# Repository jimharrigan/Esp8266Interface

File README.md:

# Esp8266Interface

A WiFi bridge between a dry-contact (or opto-isolated) signal and MQTT / HTTP, built
around an ESP-01 module. It reports the state of an external input to an MQTT topic
and/or a pair of webhook URLs, and drives a relay output in response to MQTT messages
or a polled URL.

Typical use is retrofitting network connectivity onto existing wired equipment —
a doorbell transformer, an alarm panel output, a gate contact — without modifying it.

The repository contains both halves of the project:

| Path | Contents |
| --- | --- |
| `Esp8266Interface.ino` | The Arduino firmware (single sketch) |
| `Esp8266Interface/` | KiCad schematic and PCB for the carrier board |
| `Esp8266Interface/production/` | Fabrication output: gerbers, BOM, positions, IPC netlist |
| `Esp8266Interface.sln`, `*.vcxproj` | Visual Studio + [Visual Micro](https://www.visualmicro.com/) project |
| `Esp8266Interface/test/` | Scratch KiCad project, not part of the build |

## How it works

**Input → network.** An external signal pulls `GPIO3` low, either through the on-board
PC817 optocoupler (from the `HV In` header) or by a plain contact closure on the `In3`
header. A pin-change interrupt records the new level; the main loop notices the change
and:

- publishes `Trigger` (pin low) or `Reset` (pin high) to the configured MQTT topic, and
- issues an HTTP `GET` to the configured trigger URL or reset URL.

**Network → output.** The firmware subscribes to a control topic. A payload of `1` or
`trigger` drives `GPIO1` high; anything else drives it low. `GPIO1` gates a 2N7000
low-side switch on the `Rly` header, so this is intended to energise a relay coil. The
new state is echoed back to the status topic as `Output 1` / `Output 0`.

The same output can instead — or as well — be driven by polling. If a control URL is
configured, the board fetches it every 2 s and looks at the reply: a body containing
`Trigger` closes the relay, one containing `Reset` opens it. This suits a far end that
has no MQTT broker and cannot reach in to the board, only be asked.

## Hardware

### Connectors

Silkscreen labels come from the BOM; the descriptions below are derived from the netlist.

| Ref | Label | Function |
| --- | --- | --- |
| J1 | `ESP01` | 2x4 socket for the ESP-01 module |
| J4 | `Pin` | **Power in.** Pin 1 GND, pin 2 raw DC into the LM1084-3.3 regulator |
| J5 | `Pout` | **Power out.** Pin 1 raw input rail, pin 2 regulated +3.3 V |
| J7 | `HV In` | **Isolated sense input.** Pin 1 is the common return; pin 2 feeds the optocoupler through R2 (1 k), pin 3 through R3 (68 k) + R2 for a higher-voltage source. D2 (1N4004) rectifies, so an AC source works; D1 (zener) and C5 clamp and smooth what reaches the PC817 LED via R1 (2.2 k) |
| J2 | `In3` | **Non-isolated input.** Shorting the two pins pulls `GPIO3` to GND, in parallel with the optocoupler |
| J3 | `In` | **Config-portal button.** Shorts `GPIO0` to `GPIO2`, which the firmware holds low after boot |
| J6 | `Rly` | **Relay output.** Pin 1 is the raw input rail, pin 2 the 2N7000 drain; D3 (1N4001) is the flyback diode across the coil |
| SW1 | — | Momentary **reset** for the ESP-01 (`RST` to GND) |

The zener D1 has no value in the BOM, so the usable voltage range of each `HV In` tap
depends on the part actually fitted. Work out the range for your source before relying
on it, and treat anything on `HV In` as hazardous unless you know otherwise — nothing on
the board isolates `HV In` from its own source, only from the ESP side.

### ESP-01 pin usage

| Pin | Direction | Use |
| --- | --- | --- |
| `GPIO0` | input, 3.3 k pull-up (R6) | Config-portal button, read in `loop()`; also the ESP-01 flash-mode strap |
| `GPIO1` | output | Relay drive, through R4 (47 k) into the 2N7000 gate. Also the UART TX pin |
| `GPIO2` | output, driven low | Return path for the `GPIO0` button, so the button cannot hold the board in flash mode at boot. 3.3 k pull-up (R5) |
| `GPIO3` | input, internal pull-up | Sense input, from the optocoupler or `In3`. Also the UART RX pin |

Two pins do double duty as the serial port, which shapes the firmware:

- `Serial.begin()` is called with `SERIAL_TX_ONLY` so `GPIO3` stays usable as an input.
- `GPIO1` cannot be the UART TX pin and the relay drive at the same time. The
  `DEBUG_SERIAL` switch at the top of the sketch picks one:

  | `DEBUG_SERIAL` | Behaviour |
  | --- | --- |
  | `0` (default) | Boot messages print, then `setup()` calls `Serial.end()` and claims `GPIO1` as an output. Logging stops; the relay works |
  | `1` | Serial logging stays on for the whole run; the relay output does nothing |

  Use `DBG_PRINT()` / `DBG_PRINTLN()` for any log line added after boot — plain
  `Serial` calls past the end of `setup()` go to a closed port in the default build.
- `GPIO1` toggles as TX during boot. C1 (33 µF) on the MOSFET gate with R4 gives roughly
  a 1.5 s time constant, which stops the relay chattering while the module starts up —
  at the cost of the output switching slowly.

## Building and flashing

The sketch targets the Arduino core for ESP8266 and needs these libraries:

- [WiFiManager](https://github.com/tzapu/WiFiManager) (tzapu)
- [ArduinoJson](https://arduinojson.org/) v6 — the sketch uses `DynamicJsonDocument`
- [PubSubClient](https://github.com/knolleary/pubsubclient)
- `LittleFS`, `ESP8266HTTPClient`, `WiFiClientSecure` — all part of the ESP8266 core

Build with the Arduino IDE, `arduino-cli`, or the supplied Visual Studio / Visual Micro
solution. Choose a flash layout that includes a LittleFS partition — the configuration
is stored in `/config.json` and there is nowhere to save settings without it.

The board has no USB interface and no auto-reset circuit. To flash, use an external
3.3 V USB-to-serial adapter on the ESP-01's `TX`/`RX`/`GND`, hold `GPIO0` low, and pulse
reset. Doing this with the module out of the socket avoids back-feeding the `Rly` and
`HV In` circuitry through `GPIO1` and `GPIO3`.

## Configuration

At boot the board tries the WiFi credentials WiFiManager has stored, giving up after
20 s. Failing to connect is not fatal — it keeps running while the ESP8266 keeps
retrying WiFi in the background — and it deliberately does **not** open the config
portal on its own, so a router outage cannot leave an access point running unattended
in someone's wall. If WiFi stays down for 5 minutes the board reboots (see
[Failure handling](#failure-handling)).

The portal is opened on demand instead. Press the button on `J3` and the board comes up
as an access point named **`ESP`** with the password **`1234567890`**, which is also how
you configure it on first boot, when nothing is stored yet. The portal offers the
standard WiFi and info pages plus a `param` page with these fields:

| Field | Stored as | Notes |
| --- | --- | --- |
| mqtt server | `mqtt_server` | Leave empty to disable MQTT entirely |
| mqtt port | `mqtt_port` | Defaults to 8883 |
| mqtt username | `mqtt_username` | |
| mqtt password | `mqtt_password` | |
| mqtt topic | `mqtt_topic` | Status topic the board publishes to |
| mqtt control topic | `mqtt_control_topic` | Subscribed topic for output commands; leave empty to skip |
| Trigger Url | `trigger_url` | Fetched when the input goes low, at boot if it is low, and every 10 minutes while it stays low |
| Reset Url | `reset_url` | Fetched when the input goes high, at boot if it is high, and every 10 minutes while it stays high |
| Control Url | `control_url` | Polled every 2 s for the output state; leave empty to skip |

Settings are written to `/config.json` in LittleFS and reloaded at boot. The portal
timeout is 300 s and runs non-blocking, so the rest of the loop keeps running while it
is open. Saving MQTT settings takes effect immediately: the client is re-pointed at the
new broker and any live session is dropped, so the next reconnect picks up the new
server, port, credentials and control topic without a restart.

### Messages

| Direction | Topic | Payload |
| --- | --- | --- |
| Published | `mqtt_topic` | `Trigger` when the input goes low, `Reset` when it goes high, and the current state each time the broker connection comes up |
| Published | `mqtt_topic` | `Output 1` / `Output 0` after a control message |
| Subscribed | `mqtt_control_topic` | `1` or `trigger` turns the output on; any other payload turns it off |

Payload matching is case-insensitive. An HTTP request counts as successful if the
server answers with any 2xx status; the response body is only read for the control URL.

### Control URL

A control URL is polled every 2 s and the reply decides where the output sits:

| Reply body | Effect |
| --- | --- |
| contains `Trigger` | Output on — relay energised |
| contains `Reset` | Output off |
| contains both | Treated as `Trigger` |
| contains neither | Output left as it is |
| request failed | Output left as it is |

The match is case-insensitive and anywhere in the body, so a page carrying other
markup around the word still works. Only `Output 1` / `Output 0` transitions are
published to the status topic — a poll that finds the same state as last time is
silent, so a 2 s poll does not flood the broker.

Nothing about the poll reboots the board: a control URL that stops answering leaves
the relay where it was rather than dropping it, and the next poll tries again. The
request timeout is 1.5 s, under the 2 s interval, so an unreachable server cannot
stall the loop for longer than one period, and the interval is measured from the end
of each request rather than the start. The poll runs on the first pass through the
loop, so a reboot picks the output back up immediately instead of waiting, and is
held off entirely while the config portal is open, so a bad URL can still be
corrected.

Note that the request is plain HTTP over `WiFiClient` — an `https://` control URL will
not work, and the reply is trusted as-is.

MQTT runs over `WiFiClientSecure`, but `setInsecure()` is called, so the server
certificate is not validated. Credentials are stored in plaintext in the filesystem.
Treat this as suitable for a trusted LAN, not the open internet.

### Failure handling

The input is read at boot, so its state is sent even if it never changes: the matching
URL on the first pass through the loop, and the MQTT status as soon as the broker
connects.

- **URL request fails** (no WiFi, no connection, or a non-2xx reply): the next attempt
  is due 30 s later instead of 10 minutes, and when it comes due the board reboots
  instead. After the reboot it reads the input again and makes a fresh attempt.
- **WiFi down for 5 minutes:** the board reboots. The timer counts from power-up if WiFi
  never connects, so a board with no stored credentials reboots every 5 minutes until
  the portal is used.
- **MQTT disconnected:** reconnects every 5 s, but only while WiFi is up. MQTT failures
  never cause a reboot.

Neither reboot happens while the config portal is open, and the 5-minute WiFi timer
starts again when the portal closes. A reboot turns the output off until a control
message arrives; a retained control message restores it as soon as MQTT reconnects, and
a control URL restores it on the first poll.

On the ESP8266 the first software restart after a serial upload can hang in the
bootloader, so power-cycle the board once after flashing.

## Notes

The sketch compiles clean — no warnings — against ESP8266 core 3.1.2 with
`--warnings all`, in both `DEBUG_SERIAL` configurations.

A few behaviours are deliberate rather than oversights:

- The config portal opens on the button's falling edge, not while it is held, and not
  on top of a portal that is already running. It never opens by itself on a failed
  connection.
- MQTT connection attempts are spaced `MQTT_RECONNECT_INTERVAL` (5 s) apart and
  skipped while WiFi is down, so they do not stall the loop. Saving settings in the
  portal resets that, so a new broker is tried on the next pass.
- `publishMessage()` honours its `retained` argument; every call site passes `true`, so
  every status message is retained.
- Both output paths go through `SetOutput()`, so they share one idea of where the
  output is. An MQTT command is acknowledged on the status topic whether or not it
  changed anything; a control URL poll only publishes when the level actually moves.
- If both a control topic and a control URL are configured, they fight: whichever
  spoke last wins, and the URL speaks every 2 s. Configure one or the other.

## License

GPL-3.0 — see [LICENSE](LICENSE).

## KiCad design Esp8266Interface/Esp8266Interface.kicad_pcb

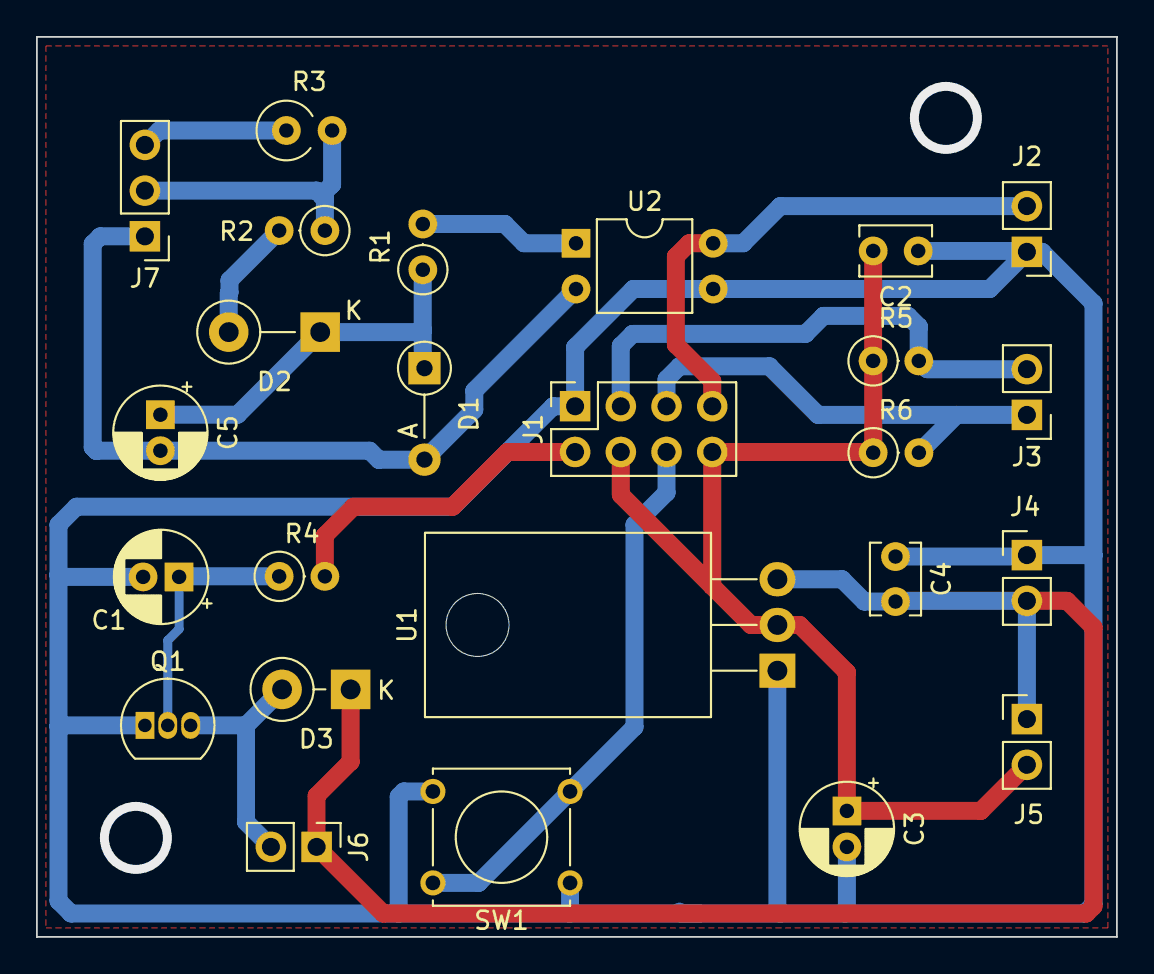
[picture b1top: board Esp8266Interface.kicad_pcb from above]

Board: 2 copper layers, 60.0 x 50.0 mm, 25 parts (0 on the bottom side), 16 nets.

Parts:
C1: 33UF; CP_Radial_D5.0mm_P2.00mm
C2, C4: .01; C_Disc_D3.8mm_W2.6mm_P2.50mm
C3: 10UF; CP_Radial_D5.0mm_P2.00mm
C5: 22UF; CP_Radial_D5.0mm_P2.00mm
D1: D_Zener; D_A-405_P5.08mm_Vertical_AnodeUp
D2: 1N4004; D_DO-41_SOD81_P5.08mm_Vertical_KathodeUp
D3: 1N4001; D_DO-41_SOD81_P3.81mm_Vertical_KathodeUp
J1: ESP01; PinHeader_2x04_P2.54mm_Vertical
J2: In3; PinHeader_1x02_P2.54mm_Vertical
J3: In; PinHeader_1x02_P2.54mm_Vertical
J4: Pin; PinHeader_1x02_P2.54mm_Vertical
J5: Pout; PinHeader_1x02_P2.54mm_Vertical
J6: Rly; PinHeader_1x02_P2.54mm_Vertical
J7: HV In; PinHeader_1x03_P2.54mm_Vertical
Q1: 2N7000; TO-92_Inline
R1: 2.2k; R_Axial_DIN0207_L6.3mm_D2.5mm_P2.54mm_Vertical
R2: 1k; R_Axial_DIN0207_L6.3mm_D2.5mm_P2.54mm_Vertical
R3: 68K; R_Axial_DIN0309_L9.0mm_D3.2mm_P2.54mm_Vertical
R4: 47K; R_Axial_DIN0207_L6.3mm_D2.5mm_P2.54mm_Vertical
R5, R6: 3.3K; R_Axial_DIN0207_L6.3mm_D2.5mm_P2.54mm_Vertical
SW1: SW_Push; SW_Tactile_Straight_KSL0Axx1LFTR
U1: LM1084-3.3; TO-220-3_Horizontal_TabDown
U2: PC817; DIP-4_W7.62mm

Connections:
+3.3V: C2.2, C3.1, J1.4 (CH_PD), J1.8 (Vcc), J5.2, R5.1, R6.1, U1.2 (VO)
GND: C1.2, C2.1, C3.2, C4.1, J1.1 (GND), J2.1, J4.1, Q1.1 (S), SW1.2, U1.1 (GND), U2.3
unnamed: C5.2, D1.2 (A), J7.1, U2.2
unnamed: C5.1, D1.1 (K), D2.1 (K), R1.1
unnamed: D2.2 (A), R2.2
unnamed: D3.2 (A), J6.2, Q1.3 (D)
unnamed: C4.2, D3.1 (K), J4.2, J5.1, J6.1, U1.3 (VI)
unnamed: J1.5 (GPIO0), J3.1, R6.2
unnamed: J1.2 (GPIO1), R4.2
unnamed: J1.3 (GPIO2), J3.2, R5.2
unnamed: J1.7 (GPIO3), J2.2, U2.4
unnamed: J1.6 (Reset), SW1.1
unnamed: J7.2, R2.1, R3.2
unnamed: J7.3, R3.1
unnamed: C1.1, Q1.2 (G), R4.1
unnamed: R1.2, U2.1

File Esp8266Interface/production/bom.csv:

Designator,Footprint,Quantity,Value,LCSC Part #
C1,CP_Radial_D5.0mm_P2.00mm,1,33UF,
"C2, C4",C_Disc_D3.8mm_W2.6mm_P2.50mm,2,.01,
C3,CP_Radial_D5.0mm_P2.00mm,1,10UF,
C5,CP_Radial_D5.0mm_P2.00mm,1,22UF,
D1,D_A-405_P5.08mm_Vertical_AnodeUp,1,D_Zener,
D2,D_DO-41_SOD81_P5.08mm_Vertical_KathodeUp,1,1N4004,
D3,D_DO-41_SOD81_P3.81mm_Vertical_KathodeUp,1,1N4001,
J1,PinHeader_2x04_P2.54mm_Vertical,1,ESP01,
J2,PinHeader_1x02_P2.54mm_Vertical,1,In3,
J3,PinHeader_1x02_P2.54mm_Vertical,1,In,
J4,PinHeader_1x02_P2.54mm_Vertical,1,Pin,
J5,PinHeader_1x02_P2.54mm_Vertical,1,Pout,
J6,PinHeader_1x02_P2.54mm_Vertical,1,Rly,
J7,PinHeader_1x03_P2.54mm_Vertical,1,HV In,
Q1,TO-92_Inline,1,2N7000,
R1,R_Axial_DIN0207_L6.3mm_D2.5mm_P2.54mm_Vertical,1,2.2k,
R2,R_Axial_DIN0207_L6.3mm_D2.5mm_P2.54mm_Vertical,1,1k,
R3,R_Axial_DIN0309_L9.0mm_D3.2mm_P2.54mm_Vertical,1,68K,
R4,R_Axial_DIN0207_L6.3mm_D2.5mm_P2.54mm_Vertical,1,47K,
"R5, R6",R_Axial_DIN0207_L6.3mm_D2.5mm_P2.54mm_Vertical,2,3.3K,
SW1,SW_Tactile_Straight_KSL0Axx1LFTR,1,SW_Push,
U1,TO-220-3_Horizontal_TabDown,1,LM1084-3.3,
U2,DIP-4_W7.62mm,1,PC817,

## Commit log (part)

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2023-06-19 Add KiCad files
2023-06-21 Circuit board
2023-07-15 PubSubClient and WiFiManager working together
2023-07-30 mostly working but custom params don't show when portal started from loop
2023-08-01 mostly working with MQTT
2023-08-08 Working with MQTT and URL but still needs cleanup and debugging removed
2023-08-13 Working on output
2023-08-14 changed to non blocking
2025-06-02 Change to use interrupts to detect changes for input_pin + old uncommitted changes
